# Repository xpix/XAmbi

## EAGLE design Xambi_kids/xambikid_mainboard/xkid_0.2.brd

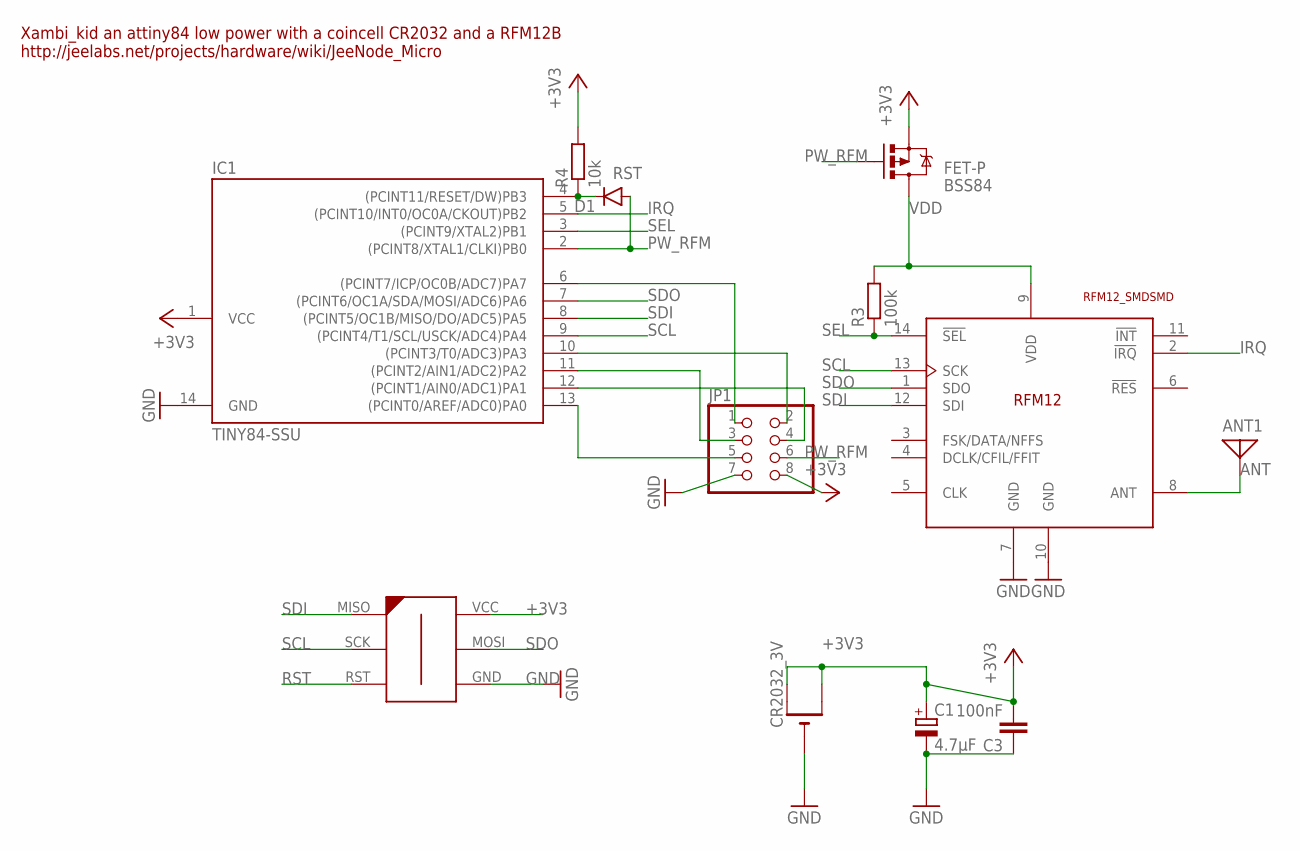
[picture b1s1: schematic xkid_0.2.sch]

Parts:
ANT1: ANTENNA; PAD-01
BSS84: FET-P; SOT23-3
C1: 4.7μF; CT3216
C3: 100nF; C0805K
CR2032_3V: CR2032THM; CR2032-THRU
D1: DIODESOD; SOD-323
IC1: TINY84-SSU; SOIC14
JP1: PINHD-2X4_2.54; 2X04
R3: 100k; R0805
R4: 10k; R0805
U$1: RFM12_SMDSMD; RFM12
U$2: AVR-ISP-6-EDGE; 6PAD_ISP

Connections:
+3V3: BSS84.2 (S), C1.+, C3.2, CR2032_3V.+1 (+), CR2032_3V.+2 (+1), IC1.1 (VCC), JP1.8, R4.2, U$2.VCC
ANT: ANT1.1, U$1.8 (ANT)
GND: C1.-, C3.1, CR2032_3V.-, IC1.14 (GND), JP1.7, U$1.7 (GND), U$1.10 (GND), U$2.GND
IRQ: IC1.5 ((PCINT10/INT0/OC0A/CKOUT)PB2), U$1.2 (!IRQ)
PA0: IC1.13 ((PCINT0/AREF/ADC0)PA0), JP1.5
PA1: IC1.12 ((PCINT1/AIN0/ADC1)PA1), JP1.4
PA2: IC1.11 ((PCINT2/AIN1/ADC2)PA2), JP1.3
PA3: IC1.10 ((PCINT3/T0/ADC3)PA3), JP1.2
PA7: IC1.6 ((PCINT7/ICP/OC0B/ADC7)PA7), JP1.1
PW_RFM: BSS84.1 (G), D1.A, IC1.2 ((PCINT8/XTAL1/CLKI)PB0), JP1.6
RST: D1.C, IC1.4 ((PCINT11/RESET/DW)PB3), R4.1, U$2.RST
SCL: IC1.9 ((PCINT4/T1/SCL/USCK/ADC4)PA4), U$1.13 (SCK), U$2.SCK
SDI: IC1.8 ((PCINT5/OC1B/MISO/DO/ADC5)PA5), U$1.12 (SDI), U$2.MISO
SDO: IC1.7 ((PCINT6/OC1A/SDA/MOSI/ADC6)PA6), U$1.1 (SDO), U$2.MOSI
SEL: IC1.3 ((PCINT9/XTAL2)PB1), R3.1, U$1.14 (!SEL)
VDD: BSS84.3 (D), R3.2, U$1.9 (VDD)

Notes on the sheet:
Xambi_kid an attiny84 low power with a coincell CR2032 and a RFM12B http://jeelabs.net/projects/hardware/wiki/JeeNode_Micro

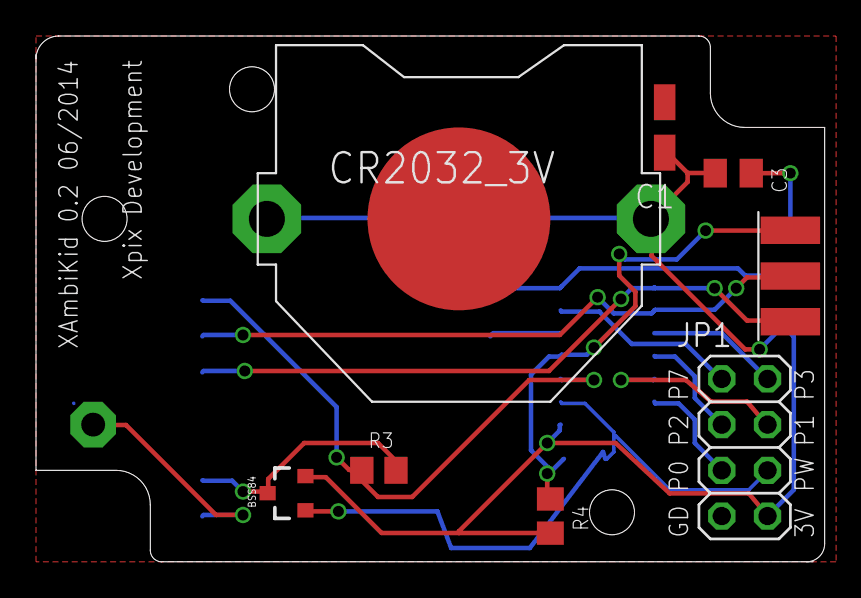
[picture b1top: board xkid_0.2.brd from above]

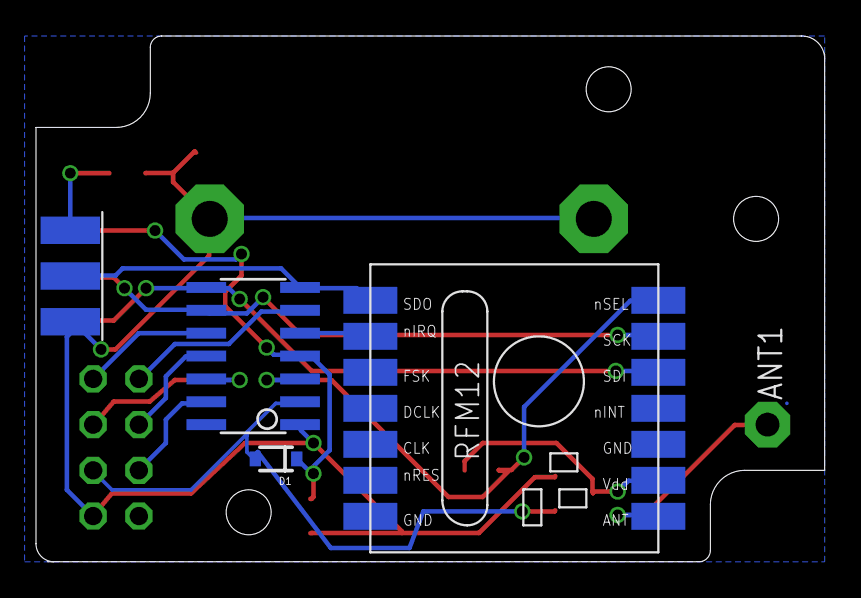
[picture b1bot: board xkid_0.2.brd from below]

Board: 2 copper layers, 43.8 x 29.2 mm, 12 parts (4 on the bottom side), 16 nets.

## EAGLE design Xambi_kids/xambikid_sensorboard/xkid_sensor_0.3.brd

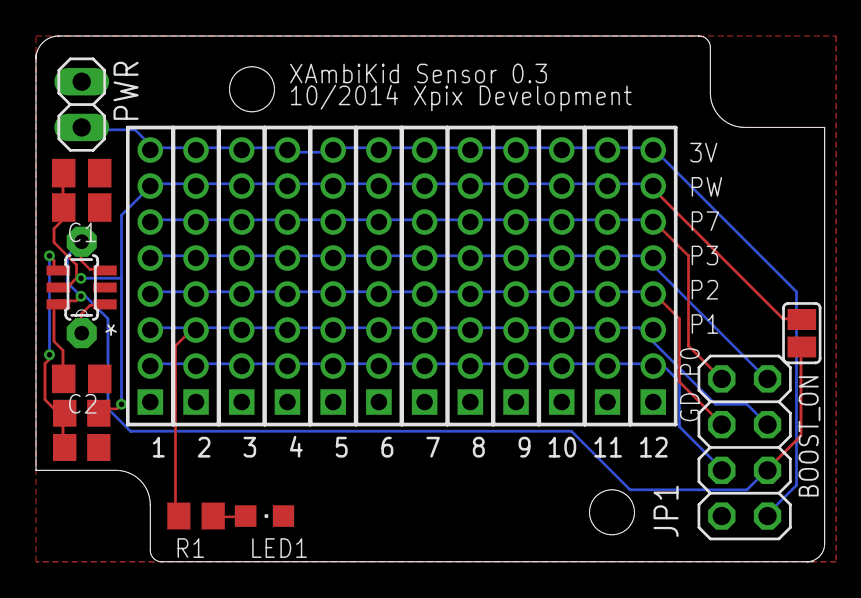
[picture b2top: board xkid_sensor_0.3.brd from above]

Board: 2 copper layers, 43.8 x 29.2 mm, 24 parts (0 on the bottom side), 12 nets.

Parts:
1, 2, 3, 4, 5, 6, 7, 8, 9, 10, 11, 12: 1X08M
BOOST: MCP1640; SOT95P270X145-6N
BOOST_ON: BoostOff?; SJ
C1, C2: 4.7mF; C0805K
C3: 100nF; C0805K
JP1: 2X04
L1: 4.7mH; 0204/5
LED1: CHIPLED_0805
PWR: 1X02
R1: R0805
R2: 330k; R0805
R3: 200k; R0805

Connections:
+3V3: 1.8, 2.8, 3.8, 4.8, 5.8, 6.8, 7.8, 8.8, 9.8, 10.8, 11.8, 12.8, JP1.8, PWR.2
BAT+: BOOST.3, BOOST.6, BOOST_ON.2, C2.2, JP1.6, L1.2
GND: 1.1, 2.1, 3.1, 4.1, 5.1, 6.1, 7.1, 8.1, 9.1, 10.1, 11.1, 12.1, BOOST.2, C1.1, C2.1, C3.1, JP1.7, LED1.C, PWR.1, R3.1
unnamed: LED1.A, R1.1
unnamed: BOOST.1, L1.1
unnamed: BOOST.4, R2.1, R3.2
PA0: 1.2, 2.2, 3.2, 4.2, 5.2, 6.2, 7.2, 8.2, 9.2, 10.2, 11.2, 12.2, JP1.5
PA1: 1.3, 2.3, 3.3, 4.3, 5.3, 6.3, 7.3, 8.3, 9.3, 10.3, 11.3, 12.3, JP1.4, R1.2
PA2: 1.4, 2.4, 3.4, 4.4, 5.4, 6.4, 7.4, 8.4, 9.4, 10.4, 11.4, 12.4, JP1.3
PA3: 1.5, 2.5, 3.5, 4.5, 5.5, 6.5, 7.5, 8.5, 9.5, 10.5, 11.5, 12.5, JP1.2
PA7: 1.6, 2.6, 3.6, 4.6, 5.6, 6.6, 7.6, 8.6, 9.6, 10.6, 11.6, 12.6, JP1.1
PW_RFM: 1.7, 2.7, 3.7, 4.7, 5.7, 6.7, 7.7, 8.7, 9.7, 10.7, 11.7, 12.7, BOOST.5, BOOST_ON.1, C1.2, C3.2, R2.2

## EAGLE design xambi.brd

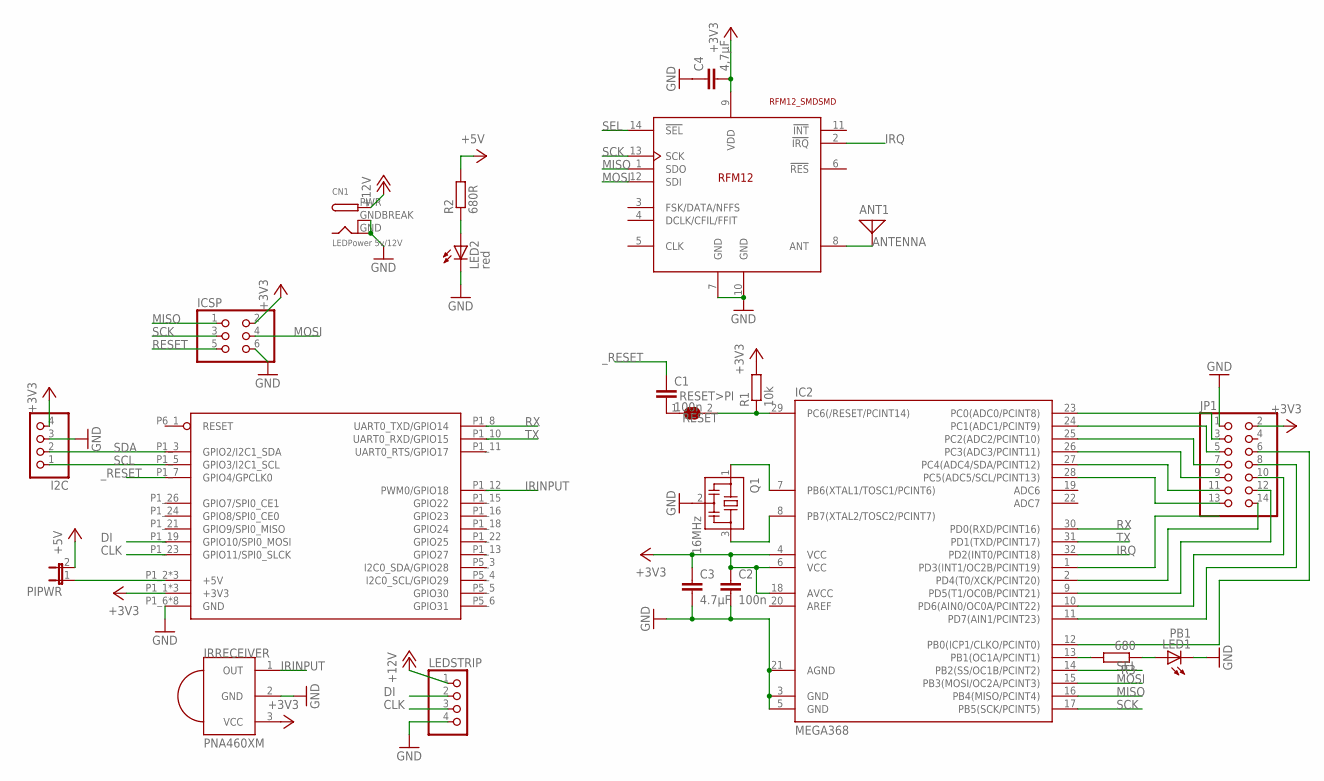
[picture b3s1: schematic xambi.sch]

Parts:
ANT1: ANTENNA; PAD-01
C1, C2: 100n; C1206
C3: 4.7µF; C1206
C4: 4,7µF; C1206
CN1: LEDPower 5v/12V; DCJACK_2MM_PTH
I2C: PINHD-1X4; 1X04
IC2: MEGA368; TQFP32-08
ICSP: PINHD-2X3; 2X03
IRRECEIVER: PNA460XM
JP1: PINHD-2X7; 2X07
LED1: PB1; CHIPLED_0805
LED2: red; CHIPLED_0603
LEDSTRIP: PINHD-1X4; 1X04
PIPWR: JP1E; JP1
Q1: 16MHz; CSTCR6M
R1: 10k; R1206
R2: 680R; R0805
R3: 680; R0805
RESET>PI: SJ
U$1: RFM12_SMDSMD; RFM12
XAMBI_SHIELD_1.1: XPIX Development / 2014; RPI-B-V2

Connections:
+3V3: C2.1, C3.1, C4.2, I2C.4, IC2.4 (VCC), IC2.6 (VCC), IC2.18 (AVCC), ICSP.2, IRRECEIVER.3 (VCC), JP1.2, R1.2, U$1.9 (VDD), XAMBI_SHIELD_1.1.P1_1 (+3V3), XAMBI_SHIELD_1.1.P1_17 (+3V3), XAMBI_SHIELD_1.1.P5_2 (+3V3)
+5V: PIPWR.2, R2.2
+12V: CN1.PWR, LEDSTRIP.1
ANTENNA: ANT1.1, U$1.8 (ANT)
CLK: LEDSTRIP.3, XAMBI_SHIELD_1.1.P1_23 (GPIO11/SPI0_SLCK)
DI: LEDSTRIP.2, XAMBI_SHIELD_1.1.P1_19 (GPIO10/SPI0_MOSI)
GND: C2.2, C3.2, C4.1, CN1.GND, CN1.GNDBREAK, I2C.3, IC2.3 (GND), IC2.5 (GND), IC2.21 (AGND), ICSP.6, IRRECEIVER.2 (GND), JP1.1, LED1.C, LED2.C, LEDSTRIP.4, Q1.2, U$1.7 (GND), U$1.10 (GND), XAMBI_SHIELD_1.1.P1_6 (GND), XAMBI_SHIELD_1.1.P1_9 (GND), XAMBI_SHIELD_1.1.P1_14 (GND), XAMBI_SHIELD_1.1.P1_20 (GND), XAMBI_SHIELD_1.1.P1_25 (GND), XAMBI_SHIELD_1.1.P5_7 (GND), XAMBI_SHIELD_1.1.P5_8 (GND), XAMBI_SHIELD_1.1.P6_2 (GND)
GPIO30: XAMBI_SHIELD_1.1.P5_5 (GPIO30)
GPIO31: XAMBI_SHIELD_1.1.P5_6 (GPIO31)
I2C0_SCL/GPIO29: XAMBI_SHIELD_1.1.P5_4 (I2C0_SCL/GPIO29)
I2C0_SDA/GPIO28: XAMBI_SHIELD_1.1.P5_3 (I2C0_SDA/GPIO28)
IRINPUT: IRRECEIVER.1 (OUT), XAMBI_SHIELD_1.1.P1_12 (PWM0/GPIO18)
IRQ: IC2.32 (PD2(INT0/PCINT18)), U$1.2 (!IRQ)
MISO: IC2.16 (PB4(MISO/PCINT4)), ICSP.1, U$1.1 (SDO)
MOSI: IC2.15 (PB3(MOSI/OC2A/PCINT3)), ICSP.4, U$1.12 (SDI)
unnamed: C1.2, RESET>PI.1
unnamed: IC2.7 (PB6(XTAL1/TOSC1/PCINT6)), Q1.1
unnamed: PIPWR.1, XAMBI_SHIELD_1.1.P1_2 (+5V), XAMBI_SHIELD_1.1.P1_4 (+5V), XAMBI_SHIELD_1.1.P5_1 (+5V)
unnamed: IC2.8 (PB7(XTAL2/TOSC2/PCINT7)), Q1.3
unnamed: LED2.A, R2.1
unnamed: LED1.A, R3.1
unnamed: IC2.13 (PB1(OC1A/PCINT1)), R3.2
PB0: IC2.12 (PB0(ICP1/CLKO/PCINT0)), JP1.6
PC0: IC2.23 (PC0(ADC0/PCINT8)), JP1.3
PC1: IC2.24 (PC1(ADC1/PCINT9)), JP1.5
PC2: IC2.25 (PC2(ADC2/PCINT10)), JP1.7
PC3: IC2.26 (PC3(ADC3/PCINT11)), JP1.9
PC4: IC2.27 (PC4(ADC4/SDA/PCINT12)), JP1.11
PC5: IC2.28 (PC5(ADC5/SCL/PCINT13)), JP1.13
PD3: IC2.1 (PD3(INT1/OC2B/PCINT19))
PD4: IC2.2 (PD4(T0/XCK/PCINT20)), JP1.14
PD5: IC2.9 (PD5(T1/OC0B/PCINT21)), JP1.12
PD6: IC2.10 (PD6(AIN0/OC0A/PCINT22)), JP1.10
PD7: IC2.11 (PD7(AIN1/PCINT23)), JP1.8
RESET: IC2.29 (PC6(/RESET/PCINT14)), ICSP.5, R1.1, RESET>PI.2, XAMBI_SHIELD_1.1.P6_1 (RESET)
RX: IC2.30 (PD0(RXD/PCINT16)), XAMBI_SHIELD_1.1.P1_8 (UART0_TXD/GPIO14)
SCK: IC2.17 (PB5(SCK/PCINT5)), ICSP.3, U$1.13 (SCK)
SCL: I2C.1, XAMBI_SHIELD_1.1.P1_5 (GPIO3/I2C1_SCL)
SDA: I2C.2, XAMBI_SHIELD_1.1.P1_3 (GPIO2/I2C1_SDA)
SEL: IC2.14 (PB2(SS/OC1B/PCINT2)), U$1.14 (!SEL)
TX: IC2.31 (PD1(TXD/PCINT17)), XAMBI_SHIELD_1.1.P1_10 (UART0_RXD/GPIO15)
_RESET: C1.1, XAMBI_SHIELD_1.1.P1_7 (GPIO4/GPCLK0)

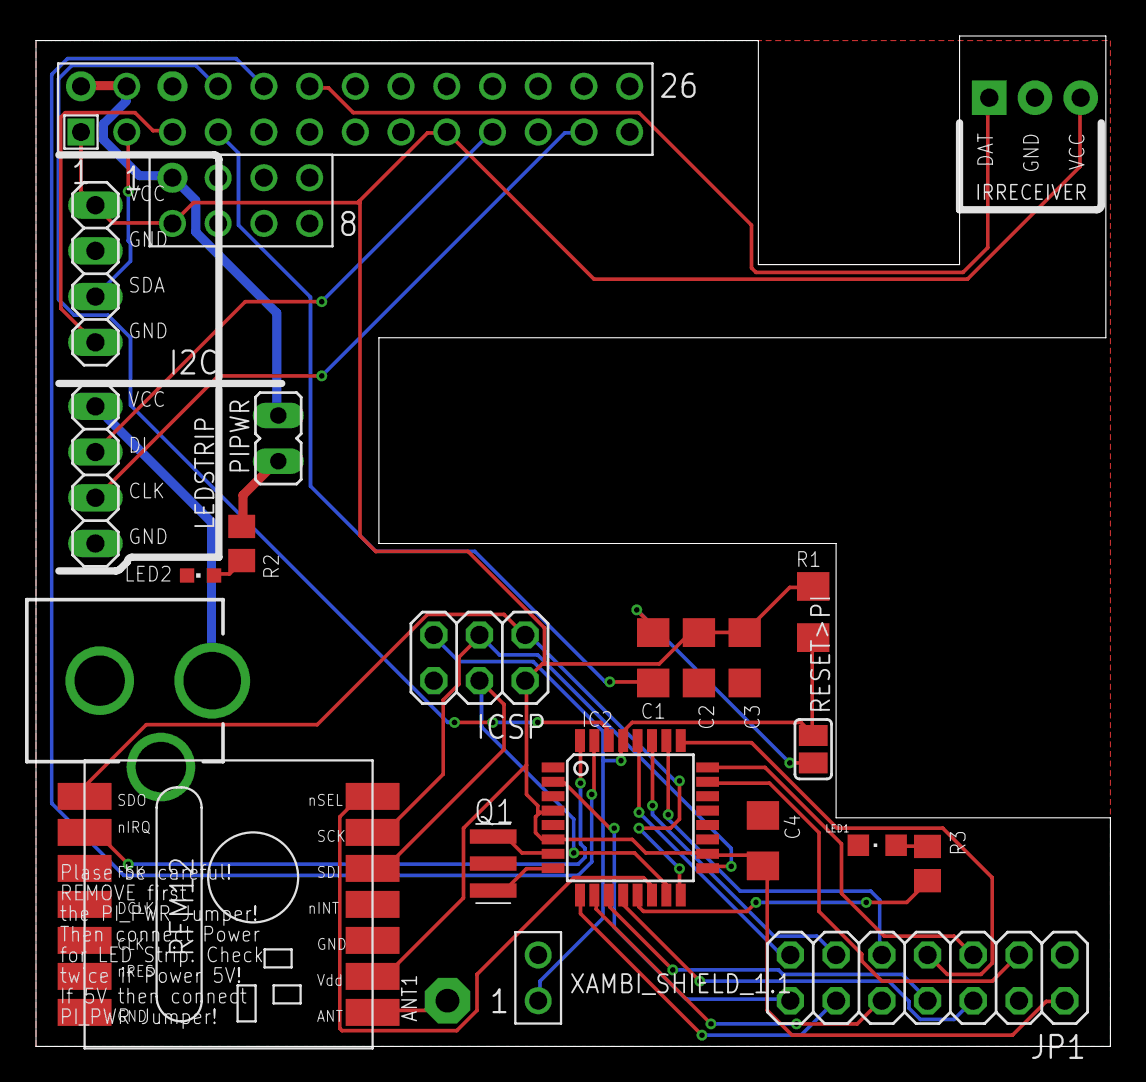
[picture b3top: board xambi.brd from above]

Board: 2 copper layers, 59.7 x 56.1 mm, 22 parts (1 on the bottom side), 37 nets.

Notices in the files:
parts and their libraries:
SparkFun-DiscreteSemi: Licensing: Creative Commons ShareAlike 4.0 International - https://creativecommons.org/licenses/by-sa/4.0
raspberry: This library stands under the CERN Open Hardware Licence.
